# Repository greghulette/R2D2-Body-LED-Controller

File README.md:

# R2D2-Body-LED-Controller
 The main controller and LED boards

The main controller and LED boards. The main controller board is being modified.  This one technically works but obsolete with the code that I wrote.  I am removing the trimpots, dip switch and some other.  The LED boards have been verified.  

These files are for CSR droids.

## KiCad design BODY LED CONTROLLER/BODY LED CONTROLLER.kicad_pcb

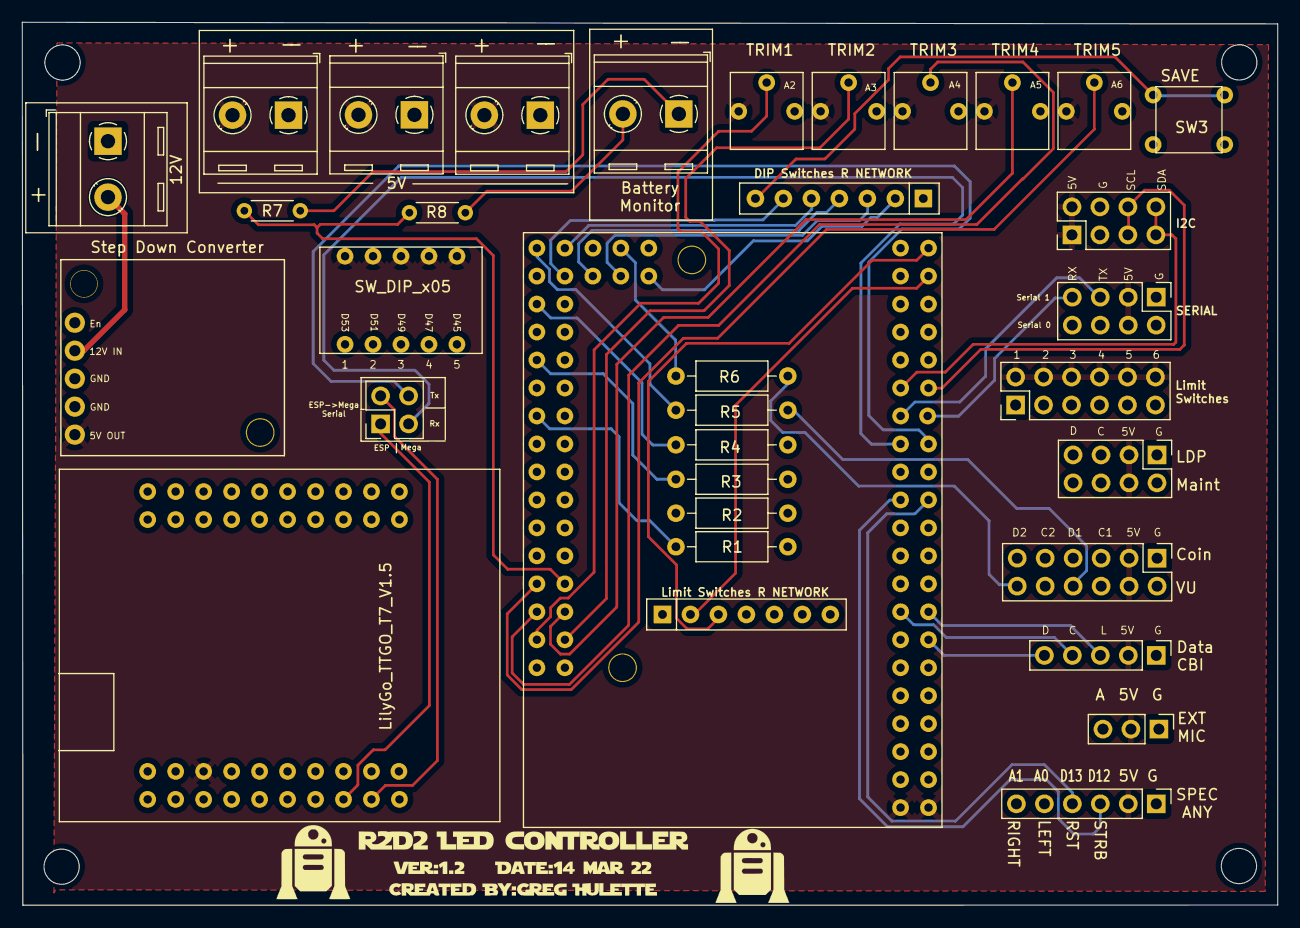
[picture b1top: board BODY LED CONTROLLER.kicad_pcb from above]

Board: 4 copper layers, 114.0 x 80.2 mm, 34 parts (0 on the bottom side), 59 nets.

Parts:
J1, J2, J3, J4, J12: Screw_Terminal_01x02; TerminalBlock_RND_205-00287_1x02_P5.08mm_Horizontal
J5: LDP/MAINT; PinHeader_2x04_P2.54mm_Vertical
J6: COIN/VU; PinHeader_2x06_P2.54mm_Vertical
J7: Data Panel/ CBI; PinHeader_1x05_P2.54mm_Vertical
J8: Spectrum Analyzer; PinHeader_1x06_P2.54mm_Vertical
J9: LIMIT; PinHeader_2x06_P2.54mm_Vertical
J10: I2C; PinHeader_2x04_P2.54mm_Vertical
J11: SERIAL; PinHeader_2x04_P2.54mm_Vertical
J13: Conn_02x02_Counter_Clockwise; PinHeader_2x02_P2.54mm_Vertical
J13#2: Conn_01x03; PinHeader_1x03_P2.54mm_Vertical
R1, R2, R3, R4, R5, R6: R_Small_US; R_Axial_DIN0207_L6.3mm_D2.5mm_P10.16mm_Horizontal
R7, R8: R_Small_US; R_Axial_DIN0204_L3.6mm_D1.6mm_P5.08mm_Horizontal
RN1, RN2: R_Network06; R_Array_SIP7
RV1: TRIM1; Potentiometer_Bourns_3362P_Top
RV2: TRIM3; Potentiometer_Bourns_3362P_Top
RV3: TRIM5; Potentiometer_Bourns_3362P_Top
RV4: TRIM2; Potentiometer_Bourns_3362P_Top
RV5: TRIM4; Potentiometer_Bourns_3362P_Top
SW1: SW_DIP_x05; DIP_Switch_TE_5435640-3
SW3: SW_DPST; Schurter_486-3458-ND_Momentary_Switch
U1: D24V550F5_Step_Down_Regulator; VoltageREG_2851
U2: LilyGo_TTGO_T7_V1.5; LILYGO_TTGO_T7_V1.5
U3: Arduino_Mega2560_Mini_Arduino_Mega2560_Mini; Arduino_Mega_2560_Pro_MINI-Updated-Corrrect

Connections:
+5V: J2.2, J3.2, J4.2, J5.3, J5.4, J6.3, J6.4, J7.2, J8.2, J9.2, J9.4, J9.6, J9.8, J9.10, J9.12, J10.1, J10.2, J11.3, J11.4, J13#2.2, RV1.3, RV2.3, RV3.3, RV4.3, RV5.3, SW1.6, SW1.7, SW1.8, SW1.9, SW1.10, U1.Vout (VOut), U2.70 (5V), U3.70 (VIN), U3.71 (VIN)
+12V: J1.2, U1.VIN
BATTERY_LEVEL: R7.1, R8.2, U3.207 (A7)
CS1_CLOCK: J6.5, U3.40 (D40)
CS1_DATA: R3.2, U3.38 (D38)
CS2_CLOCK: J6.9, U3.44 (D44)
CS2_DATA: R4.2, U3.42 (D42)
DP_CLOCK: J7.4, U3.4 (D4)
DP_DATA_IN: J7.5, U3.3 (D3)
DP_LOAD: J7.3, U3.5 (D5)
ESP_LOGIC_RX: J13.1, U2.251 (GPIO25_1)
ESP_LOGIC_TX: J13.2, U2.271 (GPIO27_1)
EXT_MIC: J13#2.3, U3.208 (A8)
GND: J1.1, J2.1, J3.1, J4.1, J5.1, J5.2, J6.1, J6.2, J7.1, J8.1, J10.3, J10.4, J11.1, J11.2, J13#2.1, RN1.1 (common), RN2.1 (common), RV1.1, RV2.1, RV3.1, RV4.1, RV5.1, SW3.1, SW3.3, U1.GND1 (GND), U1.GND2 (GND), U2.60 (GND), U2.61 (GND), U2.62 (GND), U3.62 (GND), U3.63 (GND)
JUMPER1: RN1.2 (R1), SW1.5, U3.53 (D53)
JUMPER2: RN1.3 (R2), SW1.4, U3.51 (D51)
JUMPER3: RN1.4 (R3), SW1.3, U3.49 (D49)
JUMPER4: RN1.5 (R4), SW1.2, U3.47 (D47)
JUMPER5: RN1.6 (R5), SW1.1, U3.45 (D45)
LDP_CLOCK: J5.5, U3.36 (D36)
LDP_DATA: R1.2, U3.34 (D34)
LIMIT1: J9.1, RN2.2 (R1), U3.29 (D29)
LIMIT2: J9.3, RN2.3 (R2), U3.31 (D31)
LIMIT3: J9.5, RN2.4 (R3), U3.33 (D33)
LIMIT4: J9.7, RN2.5 (R4), U3.35 (D35)
LIMIT5: J9.9, RN2.6 (R5), U3.37 (D37)
LIMIT6: J9.11, RN2.7 (R6), U3.39 (D39)
LOGIC_2560_RX: J13.3, U3.16 (D16)
LOGIC_2560_TX: J13.4, U3.17 (D17)
MAINT_CLOCK: J5.6, U3.32 (D32)
MAINT_DATA: R2.2, U3.30 (D30)
NEG: J12.2, R8.1
unnamed: J5.7, R1.1
unnamed: J5.8, R2.1
unnamed: J6.7, R3.1
unnamed: J6.8, R5.1
unnamed: J6.11, R4.1
unnamed: J6.12, R6.1
POS: J12.1, R7.2
RX0: J11.8, U3.1 (TX)
RX1: J11.7, U3.19 (D19)
SAVE: RN1.7 (R6), SW3.2, SW3.4, U3.41 (D41)
SCL: J10.5, J10.6, U3.21 (D21)
SDA: J10.7, J10.8, U3.20 (D20)
SPECTRUM_LEFT: J8.5, U3.200 (A0)
SPECTRUM_RIGHT: J8.6, U3.201 (A1)
TRIM1: RV1.2, U3.202 (A2)
TRIM2: RV4.2, U3.203 (A3)
TRIM3: RV2.2, U3.204 (A4)
TRIM4: RV5.2, U3.205 (A5)
TRIM5: RV3.2, U3.206 (A6)
TX0: J11.6, U3.0 (RX)
TX1: J11.5, U3.18 (D18)
VU1_CLOCK: J6.6, U3.48 (D48)
VU1_DATA: R5.2, U3.46 (D46)
VU2_CLOCK: J6.10, U3.52 (D52)
VU2_DATA: R6.2, U3.50 (D50)
VU_RESET: J8.4, U3.13 (D13)
VU_STROBE: J8.3, U3.12 (D12)

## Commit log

2022-03-14 Initial Submission.
